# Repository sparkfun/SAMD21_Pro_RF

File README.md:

SparkFun Pro RF - LoRa, 915MHz (SAMD21)
======================================

[*SparkFun SAMD21 Pro RF LoRa 915MHz (WRL-14916)*](https://www.sparkfun.com/products/14916)

The [SparkFun SAMD21 Pro RF](https://www.sparkfun.com/products/14916) is the fated meeting of a SAMD21 and a long-range [RFM95W LoRa®-enabled radio](https://cdn.sparkfun.com/assets/a/9/6/1/0/RFM95W-V2.0.pdf). The outcome is a compact, blazing fast MCU with excellent point to point data transmission in the 915MHz ISM band with LoRa Capabilities. The SAMD21 Pro RF comes with a LiPo connector, an on-board LiPo charger, and a slide switch to power the board on and off. The board programs over a reinforced Micro-B connector with a slim reset button that fits nicely on the side of the board. We’ve even added our popular [Qwiic](https://www.sparkfun.com/qwiic) connector to the edge of the board making it incredibly easy to add sensors and actuators without the need for solder or a soldering iron!

Repository Contents
-------------------

* **/Hardware** - Eagle design files (.brd, .sch)
* **/Production** - Production panel files (.brd)

Documentation
--------------
* **[Hookup Guide](https://learn.sparkfun.com/tutorials/sparkfun-samd21-pro-rf-hookup-guide)** - Basic hookup guide the SAMD21 Pro RF going over the point to point radio capabilities of the radio module and how to set up and use LoRaWAN. 
* **[Arduino Example Code](https://github.com/sparkfun/Sparkfun_SAMD21_Pro_RF_Arduino_Examples)** - Code for the radio module including point to point and LoRaWAN examples.
* **[SAMD21G18A-AU Datasheet](https://cdn.sparkfun.com/datasheets/Dev/Arduino/Boards/Atmel-42181-SAM-D21_Datasheet.pdf)** - Datasheet for the SAMD21G
* **[HopeRF RFM95W Radio Module](https://cdn.sparkfun.com/assets/a/9/6/1/0/RFM95W-V2.0.pdf)** - Datasheet for the RFM95W radio module.

License Information
-------------------

This product is _**open source**_! 

Please review the LICENSE.md file for license information. 

If you have any questions or concerns on licensing, please contact techsupport@sparkfun.com.

Distributed as-is; no warranty is given.

- Your friends at SparkFun.

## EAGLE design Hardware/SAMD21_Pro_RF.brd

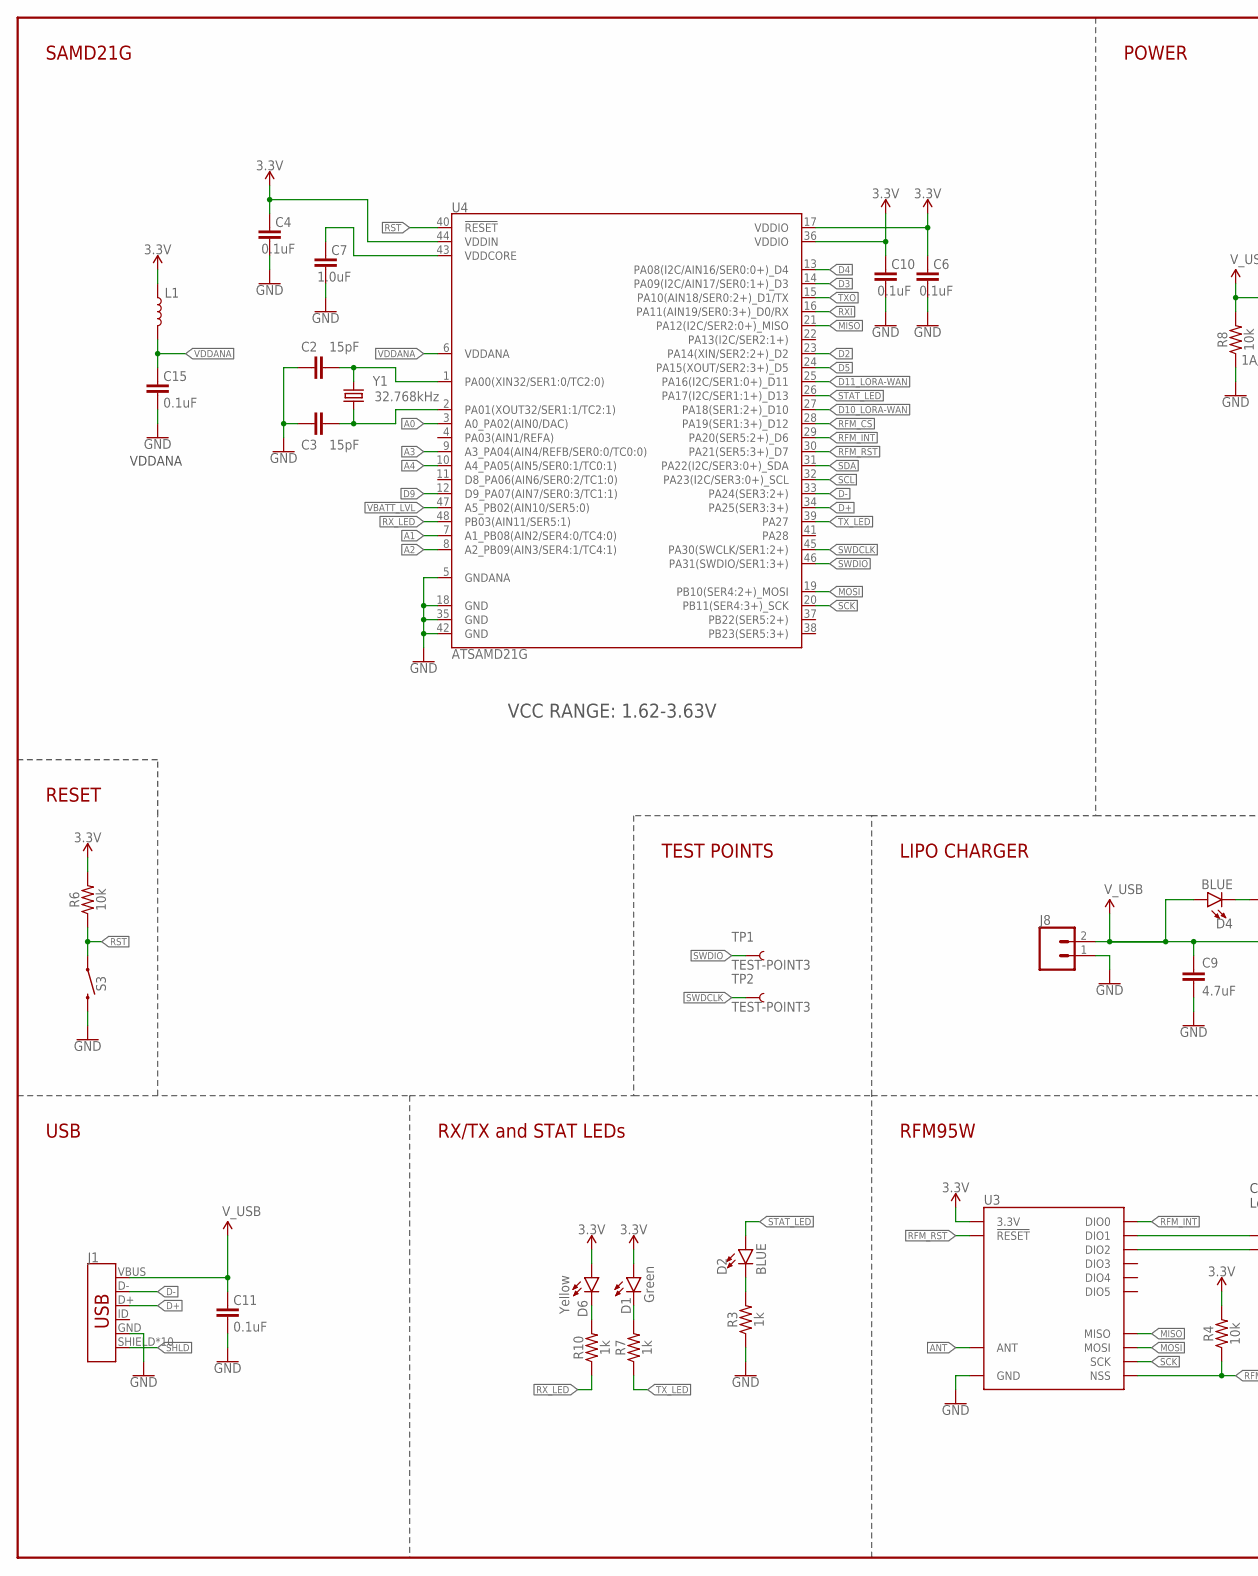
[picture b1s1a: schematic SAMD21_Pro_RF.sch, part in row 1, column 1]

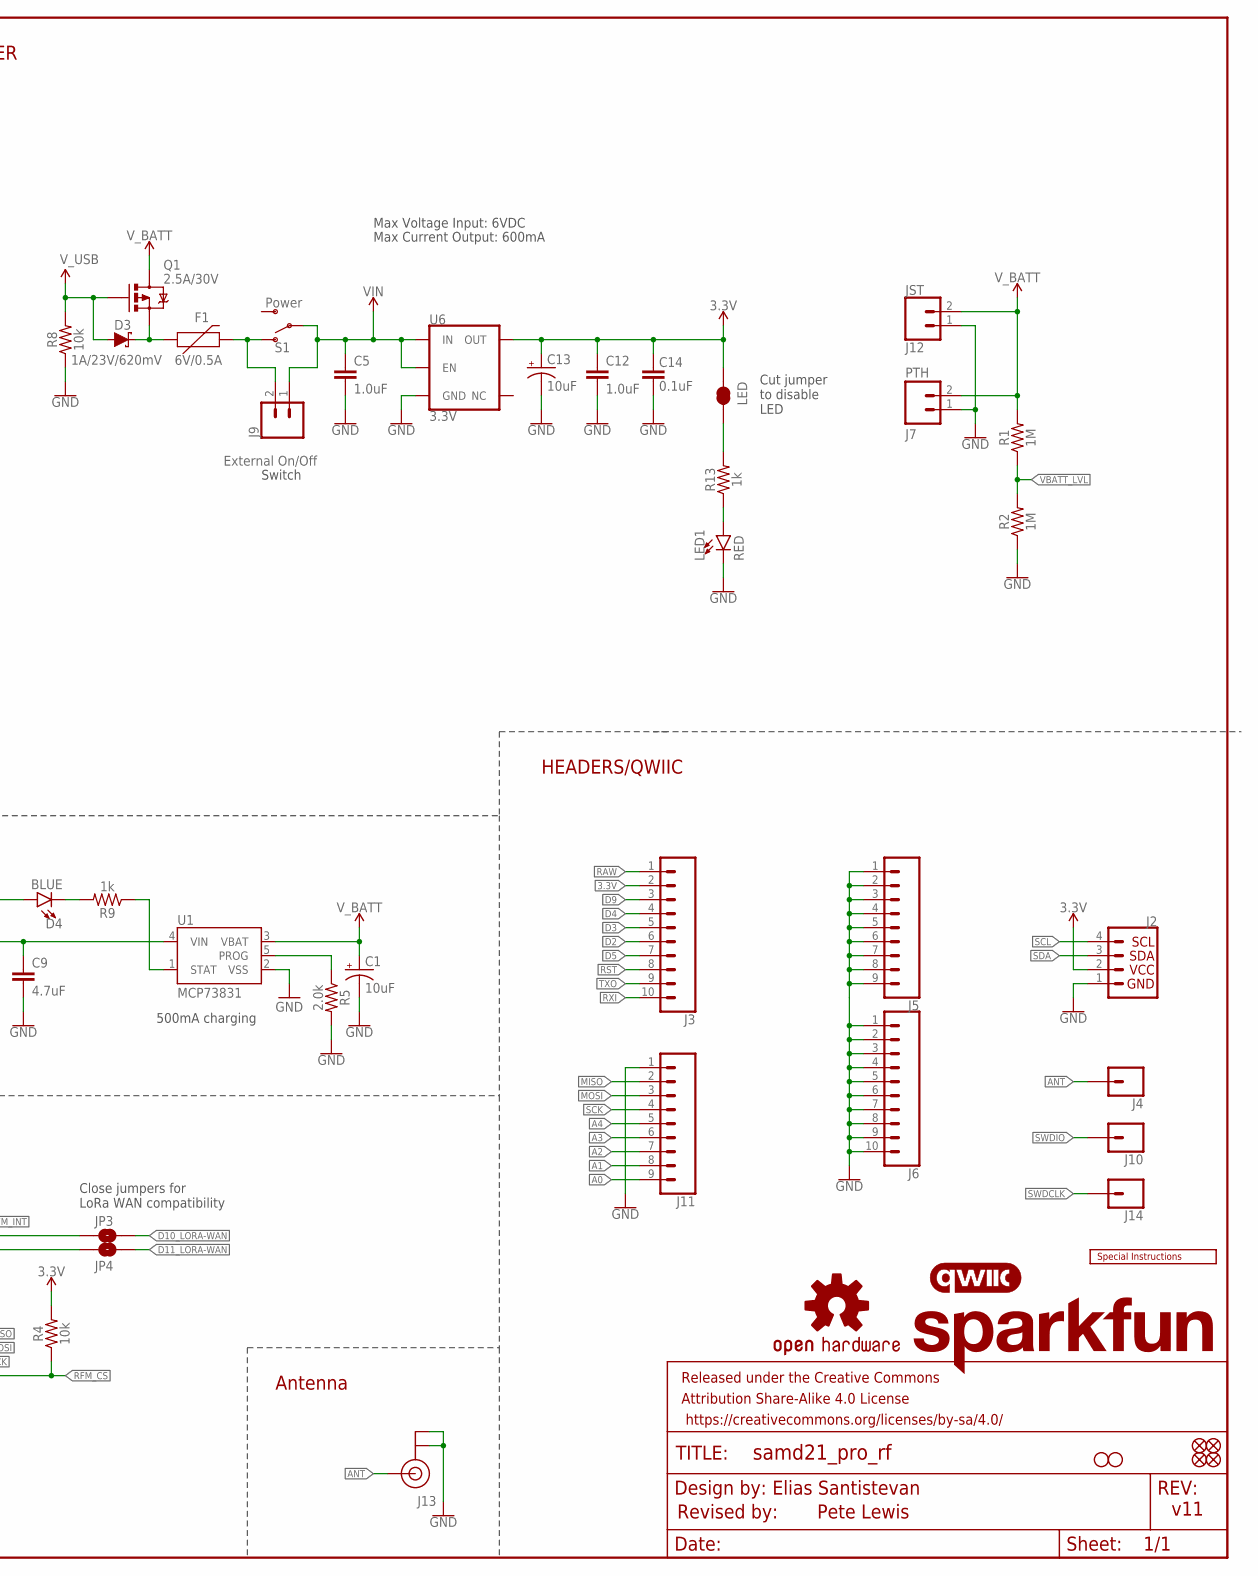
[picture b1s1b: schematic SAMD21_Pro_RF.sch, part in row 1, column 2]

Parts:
C1, C13: 10uF; EIA3216
C2, C3: 15pF; 0603
C4, C6, C10, C11, C14, C15: 0.1uF; 0603
C5, C7, C12: 1.0uF; 0603
C9: 4.7uF; 0603
D1: Green; LED-0603
D2, D4: BLUE; LED-0603
D3: 1A/23V/620mV; SOD-323
D6: Yellow; LED-0603
F1: 6V/0.5A; 1206
FD1, FD2, FD3, FD4: FIDUCIAL1X2; FIDUCIAL-1X2
FRAME2: FRAME-LEDGER; CREATIVE_COMMONS
H1, H2: STAND-OFFTIGHT; STAND-OFF-TIGHT
J1: USB_MICRO-B_HALF_PTH_MILL; USB-MICROB-PTH-MILL
J2: QWIIC_CONNECTORJS-1MM; 1X04_1MM_RA
J3, J6: CONN_10NO_SILK_PTH_FEMALE; 1X10_NO_SILK
J4, J10, J14: CONN_01PTH_NO_SILK_YES_STOP; 1X01_NO_SILK
J5, J11: CONN_09NO_SILK; 1X09_NO_SILK
J7: PTH; 1X02_NO_SILK
J8: CONN_021X02_NO_SILK; 1X02_NO_SILK
J9: External On/Off; 1X02_NO_SILK
J12: JST; JST-2-SMD
J13: U.FL
JP3, JP4: JUMPER-SMT_2_NO_SILK; SMT-JUMPER_2_NO_SILK
L1: INDUCTORFB-30OHM; 0603
LED: JUMPER-SMT_2_NC_TRACE_SILK; SMT-JUMPER_2_NC_TRACE_SILK
LED1: RED; LED-0603
LOGO1: OSHW-LOGOMINI; OSHW-LOGO-MINI
LOGO2: SFE_LOGO_NAME.1_INCH; SFE_LOGO_NAME_.1
LOGO3: QWIIC_LOGO_5MM; QWIIC_5MM
Q1: 2.5A/30V; SOT23-3@1
R1, R2: 1M; 0603
R3, R7, R9, R10, R13: 1k; 0603
R4, R6, R8: 10k; 0603
R5: 2.0k; 0603
S1: Power; SWITCH_SPST_SMD_A
S3: MOMENTARY-SWITCH-SPST-SMD-RIGHT-ANGLE; TACTILE_SWITCH_SMD_RIGHT_ANGLE
TP1, TP2: TEST-POINT3; PAD.03X.03
U1: MCP73831; SOT23-5
U3: RFM95W; RFM95/96/97/98W
U4: ATSAMD21G; QFN-48_NO_EXPOSED_PAD
U6: 3.3V; SOT23-5
U$26: SPECIAL_INSTRUCTIONS-ORDERING; ORDERING_INSTRUCTIONS
Y1: 32.768kHz; CRYSTAL-SMD-3.2X1.5MM

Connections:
3.3V: C4.2, C6.2, C10.2, C12.1, C13.+, C14.2, D1.A, D6.A, J2.2, J3.2, L1.1, LED.1, R4.2, R6.2, U3.3.3V, U4.17 (VDDIO), U4.36 (VDDIO), U4.44 (VDDIN), U6.5 (OUT)
!RFM_CS: R4.1, U3.NSS, U4.28 (PA19(SER1:3+)_D12)
!RFM_RST: U3.!RESET, U4.30 (PA21(SER5:3+)_D7)
!RST: J3.8, R6.1, S3.1, U4.40 (!RESET!)
A0: J11.9, U4.3 (A0_PA02(AIN0/DAC))
A1: J11.8, U4.7 (A1_PB08(AIN2/SER4:0/TC4:0))
A2: J11.7, U4.8 (A2_PB09(AIN3/SER4:1/TC4:1))
A3: J11.6, U4.9 (A3_PA04(AIN4/REFB/SER0:0/TC0:0))
A4: J11.5, U4.10 (A4_PA05(AIN5/SER0:1/TC0:1))
ANT: J4.1, J13.FEED (SIGNAL), U3.ANT
CHARGE_STAT: R9.1, U1.1 (STAT)
D2: J3.6, U4.23 (PA14(XIN/SER2:2+)_D2)
D3: J3.5, U4.14 (PA09(I2C/AIN17/SER0:1+)_D3)
D4: J3.4, U4.13 (PA08(I2C/AIN16/SER0:0+)_D4)
D5: J3.7, U4.24 (PA15(XOUT/SER2:3+)_D5)
D9: J3.3, U4.12 (D9_PA07(AIN7/SER0:3/TC1:1))
D10_LORA-WAN: JP3.2, U4.27 (PA18(SER1:2+)_D10)
D11_LORA-WAN: JP4.2, U4.25 (PA16(I2C/SER1:0+)_D11)
D+: J1.D+, U4.34 (PA25(SER3:3+))
D-: J1.D-, U4.33 (PA24(SER3:2+))
GND: C1.-, C2.1, C3.1, C4.1, C5.2, C6.1, C7.1, C9.2, C10.1, C11.1, C12.2, C13.-, C14.1, C15.1, J1.GND, J2.1, J5.1, J5.2, J5.3, J5.4, J5.5, J5.6, J5.7, J5.8, J5.9, J6.1, J6.2, J6.3, J6.4, J6.5, J6.6, J6.7, J6.8, J6.9, J6.10, J7.1, J8.1, J11.1, J12.1 (2), J13.1 (GND), J13.2 (GND), LED1.C, R2.1, R3.1, R5.2, R8.1, S3.2, U1.2 (VSS), U3.GND@1 (GND), U3.GND@2 (GND), U3.GND@3 (GND), U4.5 (GNDANA), U4.18 (GND), U4.35 (GND), U4.42 (GND), U6.2 (GND)
MISO: J11.2, U3.MISO, U4.21 (PA12(I2C/SER2:0+)_MISO)
MOSI: J11.3, U3.MOSI, U4.19 (PB10(SER4:2+)_MOSI)
unnamed: D6.C, R10.2
unnamed: D1.C, R7.2
unnamed: D2.C, R3.2
unnamed: C7.2, U4.43 (VDDCORE)
unnamed: LED.2, R13.2
unnamed: C2.2, U4.1 (PA00(XIN32/SER1:0/TC2:0)), Y1.P$2 (2)
unnamed: C3.2, U4.2 (PA01(XOUT32/SER1:1/TC2:1)), Y1.P$1 (1)
unnamed: D4.C, R9.2
unnamed: F1.2, J9.2, S1.1 (O)
unnamed: R5.1, U1.5 (PROG)
unnamed: JP3.1, U3.DIO1
unnamed: JP4.1, U3.DIO2
unnamed: LED1.A, R13.1
RAW: D3.C, F1.1, J3.1, Q1.2 (S)
RFM_INT: U3.DIO0, U4.29 (PA20(SER5:2+)_D6)
RXI: J3.10, U4.16 (PA11(AIN19/SER0:3+)_D0/RX)
RX_LED: R10.1, U4.48 (PB03(AIN11/SER5:1))
SCK: J11.4, U3.SCK, U4.20 (PB11(SER4:3+)_SCK)
SCL: J2.4, U4.32 (PA23(I2C/SER3:0+)_SCL)
SDA: J2.3, U4.31 (PA22(I2C/SER3:0+)_SDA)
SHLD: J1.SHIELD, J1.SHIELD2 (SHIELD), J1.SHIELD3 (SHIELD), J1.SHIELD4 (SHIELD), J1.SHIELD5 (SHIELD), J1.SHIELD6 (SHIELD), J1.SHIELD7 (SHIELD), J1.SHIELD8 (SHIELD), J1.SHIELD9 (SHIELD), J1.SHIELD10 (SHIELD)
STAT_LED: D2.A, U4.26 (PA17(I2C/SER1:1+)_D13)
SWDCLK: J14.1, TP2.P$1, U4.45 (PA30(SWCLK/SER1:2+))
SWDIO: J10.1, TP1.P$1, U4.46 (PA31(SWDIO/SER1:3+))
TXO: J3.9, U4.15 (PA10(AIN18/SER0:2+)_D1/TX)
TX_LED: R7.1, U4.39 (PA27)
VBATT_LVL: R1.1, R2.2, U4.47 (A5_PB02(AIN10/SER5:0))
VDDANA: C15.2, L1.2, U4.6 (VDDANA)
VIN: C5.1, J9.1, S1.2, U6.1 (IN), U6.3 (EN)
V_BATT: C1.+, J7.2, J12.2 (1), Q1.3 (D), R1.2, U1.3 (VBAT)
V_USB: C9.1, C11.2, D3.A, D4.A, J1.VBUS, J8.2, Q1.1 (G), R8.2, U1.4 (VIN)

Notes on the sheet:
Max Voltage Input: 6VDC
Max Current Output: 600mA
500mA charging
Close jumpers for LoRa WAN compatibility
VDDANA
SAMD21G
Elias Santistevan
v11
POWER
LIPO CHARGER
RFM95W
RESET
HEADERS/QWIIC
USB
TEST POINTS
Antenna
RX/TX and STAT LEDs
Switch
Revised by:
Pete Lewis
Cut jumper to disable LED
VCC RANGE: 1.62-3.63V

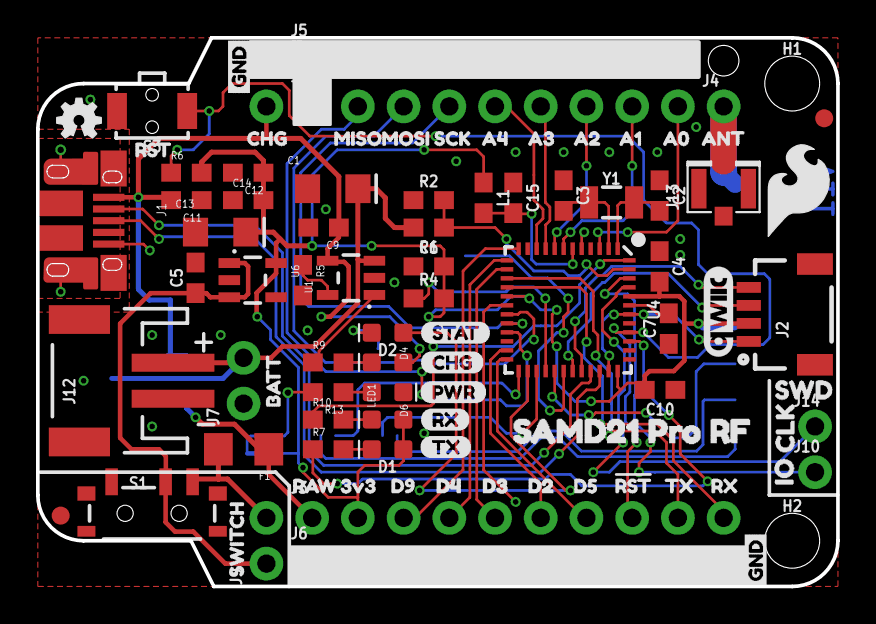
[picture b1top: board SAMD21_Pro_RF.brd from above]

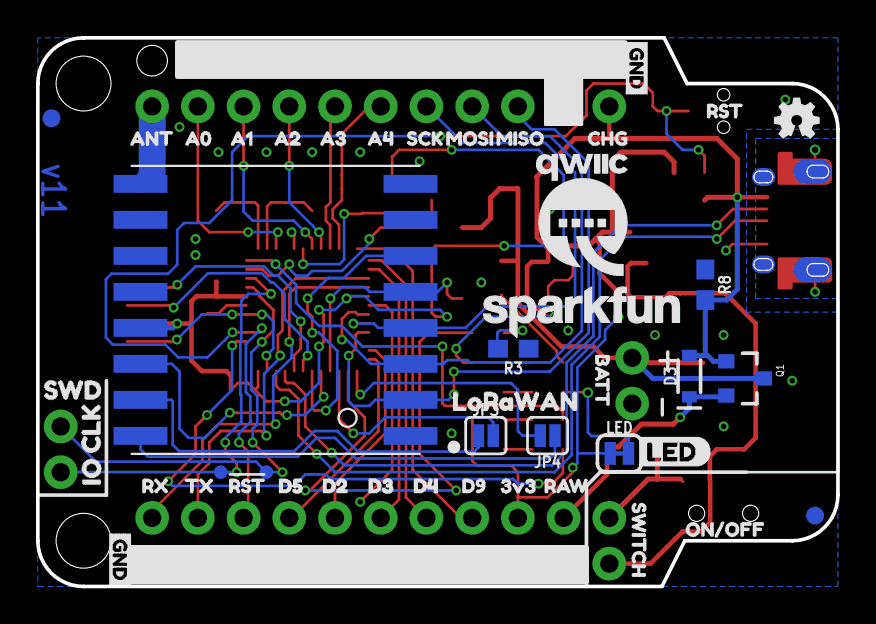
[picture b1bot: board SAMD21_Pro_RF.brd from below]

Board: 2 copper layers, 44.5 x 30.5 mm, 140 parts (47 on the bottom side), 54 nets.

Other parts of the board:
U$1: SAMD21_PRO_RF0
U$2, U$18: D20
U$3, U$42: A43
U$4, U$43: A34
U$5, U$44: A25
U$6, U$45: A16
U$7, U$46: A07
U$8, U$47: MISO8
U$9, U$48: MOSI9
U$10, U$49: SCK10
U$11, U$50: ANT11
U$12, U$17, U$38, U$62: GND0
U$13, U$28, U$36, U$41: RST2
U$14, U$40, U$65: CHG1
U$15, U$16: D90
U$19, U$73: RX2
U$20, U$21: D30
U$22, U$31: D40
U$23, U$53: 3V320
U$24, U$52: RAW21
U$25: LORA0
U$27, U$37: SWITCH23
U$29, U$32: BATT25
U$30: QWIIC-LOGO-MEDIUM
U$33: D50
U$34, U$64: IO3
U$35: WAN1
U$39: ON#OFF0
U$51: SFE_LOGO_FLAME_.2
U$54: STAT0
U$55: D514
U$56, U$60: CLK4
U$57, U$69: TX3
U$58, U$59: SWD2
U$61: OSHW-LOGO-MINI
U$63: PWR-()-03
U$66: LED0
U$70: TX6
U$72: RX7

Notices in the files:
parts and their libraries:
SparkFun-Capacitors: Licensing: CC v3.0 Share-Alike You are welcome to use this library for commercial purposes.
SparkFun-LED: Licensing: Creative Commons ShareAlike 4.0 International - https://creativecommons.org/licenses/by-sa/4.0
SparkFun-Aesthetics: Released under the Creative Commons
